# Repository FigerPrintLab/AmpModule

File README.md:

# AmpModule (Stakx)

Hardware implementation for the Stakx amplifier's front panel PCB.

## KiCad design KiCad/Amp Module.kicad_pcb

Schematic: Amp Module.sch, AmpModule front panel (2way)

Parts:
C1, C2: 22p; C_0805_2012Metric
C3, C4, C5, C6, C11, C12, C13, C14: 0.1uF; C_0805_2012Metric
C7: 10uF; CP_Elec_4x5.3
C8: 22uF; CP_Elec_4x5.3
C9, C10: 1u; C_0805_2012Metric
D1, D2: D_Small; D_MiniMELF
D3: READY1; LED_Rectangular_W5.0mm_H5.0mm
D4: READY2; LED_Rectangular_W5.0mm_H5.0mm
D5: ON; LED_Rectangular_W5.0mm_H5.0mm
J1: DSP; IDC-Header_2x17_P2.54mm_Vertical
J2: LITEMOD; IDC-Header_2x17_P2.54mm_Vertical
R1, R2: 8.2k; R_0805_2012Metric
R3, R4, R11, R17: 2.7k; R_0805_2012Metric
R5, R6, R13, R19: 1k; R_0805_2012Metric
R7, R8, R12, R18: 1.8k; R_0805_2012Metric
R9, R15: 5.6k; R_0805_2012Metric
R10, R16: 3.9k; R_0805_2012Metric
R14, R20: 470; R_0805_2012Metric
R21, R22, R27, R28, R29: 180; R_0805_2012Metric
R23, R24: 51k; R_0805_2012Metric
R25, R26: 22k; R_0805_2012Metric
SW1, SW2: Alps_SRBV170701
SW3: MUTE1; TL2-NNS7
SW4: MUTE2; TL2-NNS7
U1, U2: NE5532; SOIC-8_3.9x4.9mm_P1.27mm
U3: AMS1117-5.0; SOT-223-3_TabPin2
U4: TL072; SOIC-8_3.9x4.9mm_P1.27mm
U5: 74LVC2G14; SOT-23-6
U6: 74VHC74; TSSOP-14_4.4x5mm_P0.65mm
U7: 74HC08; SOIC-14_3.9x8.7mm_P1.27mm

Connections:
+5VDC: J1.4, J1.31, J2.4, J2.31
+5V_REG: C8.1, C11.2, C12.2, C13.2, C14.2, D5.2 (A), R21.1, R22.1, R23.1, R24.1, U3.2 (VO), U4.8 (V+), U5.5 (VCC), U6.1 (~R), U6.4 (~S), U6.10 (~S), U6.13 (~R), U6.14 (VCC), U7.14 (VCC); also elsewhere on the board
+12VDC: C5.1, C6.1, C7.1, J1.13, J1.22, J2.13, J2.22, U1.8 (V+), U2.8 (V+), U3.3 (VI)
+VCCMON: J1.16, J1.19, J2.16, J2.19
-12VDC: C3.1, C4.1, J1.14, J1.21, J2.14, J2.21, U1.4 (V-), U2.4 (V-)
-VCCMON: J1.17, J1.18, J2.17, J2.18
DSP_MUTE1: J1.15, U7.2
DSP_MUTE2: J1.20, U7.4
DSP_OUT1+: J1.6, R1.1
DSP_OUT1-: J1.7
DSP_OUT2+: J1.29, R2.1
DSP_OUT2-: J1.28
GND: C3.2, C4.2, C5.2, C6.2, C7.2, C8.2, C9.2, C10.2, C11.1, C12.1, C13.1, C14.1, J1.5, J1.8, J1.27, J1.30, J2.5, J2.8, J2.27, J2.30, R3.2, R4.2, R7.1, R8.1, R27.2, R28.2, R29.2, SW3.1, SW4.1, U3.1 (GND), U4.4 (V-), U5.2 (GND), U6.7 (GND), U7.7 (GND); also elsewhere on the board
IOUT1MON: J1.11, J2.11
IOUT2MON: J1.24, J2.24
LM_IN1+: J2.6, U1.6 (-), U1.7
LM_IN1-: J2.7
LM_IN2+: J2.29, U2.6 (-), U2.7
LM_IN2-: J2.28
LM_MUTE1: J2.15, SW3.3 (K), U7.3
LM_MUTE2: J2.20, SW4.3 (K), U7.6
unnamed: C1.1, SW1.1, SW1.10, U1.1, U1.5 (+)
unnamed: C1.2, R7.2, R9.1, R10.1, R11.1, R12.1, R13.1, R14.1, SW1.8, U1.2 (-)
unnamed: C2.1, SW2.1, SW2.10, U2.1, U2.5 (+)
unnamed: C2.2, R8.2, R15.1, R16.1, R17.1, R18.1, R19.1, R20.1, SW2.8, U2.2 (-)
unnamed: C9.1, D1.1 (K), R25.1, U5.1
unnamed: C10.1, D2.1 (K), R26.1, U5.3
unnamed: D1.2 (A), R23.2, R25.2, SW3.2
unnamed: D2.2 (A), R24.2, R26.2, SW4.2
unnamed 29: D3.1 (K), R27.1; also elsewhere on the board
unnamed: D4.1 (K), R28.1
unnamed: D5.1 (K), R29.1
unnamed: R1.2, R3.1, R5.2
unnamed: R2.2, R4.1, R6.2
unnamed: R5.1, U1.3 (+)
unnamed: R6.1, U2.3 (+)
unnamed: R9.2, SW1.2
unnamed: R10.2, SW1.3
unnamed: R11.2, SW1.4
unnamed: R12.2, SW1.5
unnamed: R13.2, SW1.6
unnamed: R14.2, SW1.7
unnamed: R15.2, SW2.2
unnamed: R16.2, SW2.3
unnamed: R17.2, SW2.4
unnamed: R18.2, SW2.5
unnamed: R19.2, SW2.6
unnamed: R20.2, SW2.7
unnamed: R21.2, SW3.4 (A)
unnamed: R22.2, SW4.4 (A)
unnamed: U5.4, U6.11 (C)
unnamed: U5.6, U6.3 (C)
unnamed: U6.2 (D), U6.6 (~Q)
unnamed: U6.5 (Q), U7.1
unnamed: U6.9 (Q), U7.5
unnamed: U6.8 (~Q), U6.12 (D)
PROTECT1: J1.10, J2.10; also elsewhere on the board
PROTECT2: J1.25, J2.25; also elsewhere on the board
READY1: J2.2, U4.3 (+)
READY2: J2.33, U4.5 (+)
READY_DSP1: D3.2 (A), J1.2, U4.1, U4.2 (-); also elsewhere on the board
READY_DSP2: D4.2 (A), J1.33, U4.6 (-), U4.7
RESERVED_A: J1.3, J2.3
RESERVED_B: J1.32, J2.32
SDPWS: J1.1, J1.34, J2.1, J2.34
TEMPMON12: J1.12, J1.23, J2.12, J2.23; also elsewhere on the board
VOUT1MON: J1.9, J2.9; also elsewhere on the board
VOUT2MON: J1.26, J2.26; also elsewhere on the board

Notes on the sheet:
IDC
MUTE
AUDIO
STATUS LEDs
REGULATOR
check cap

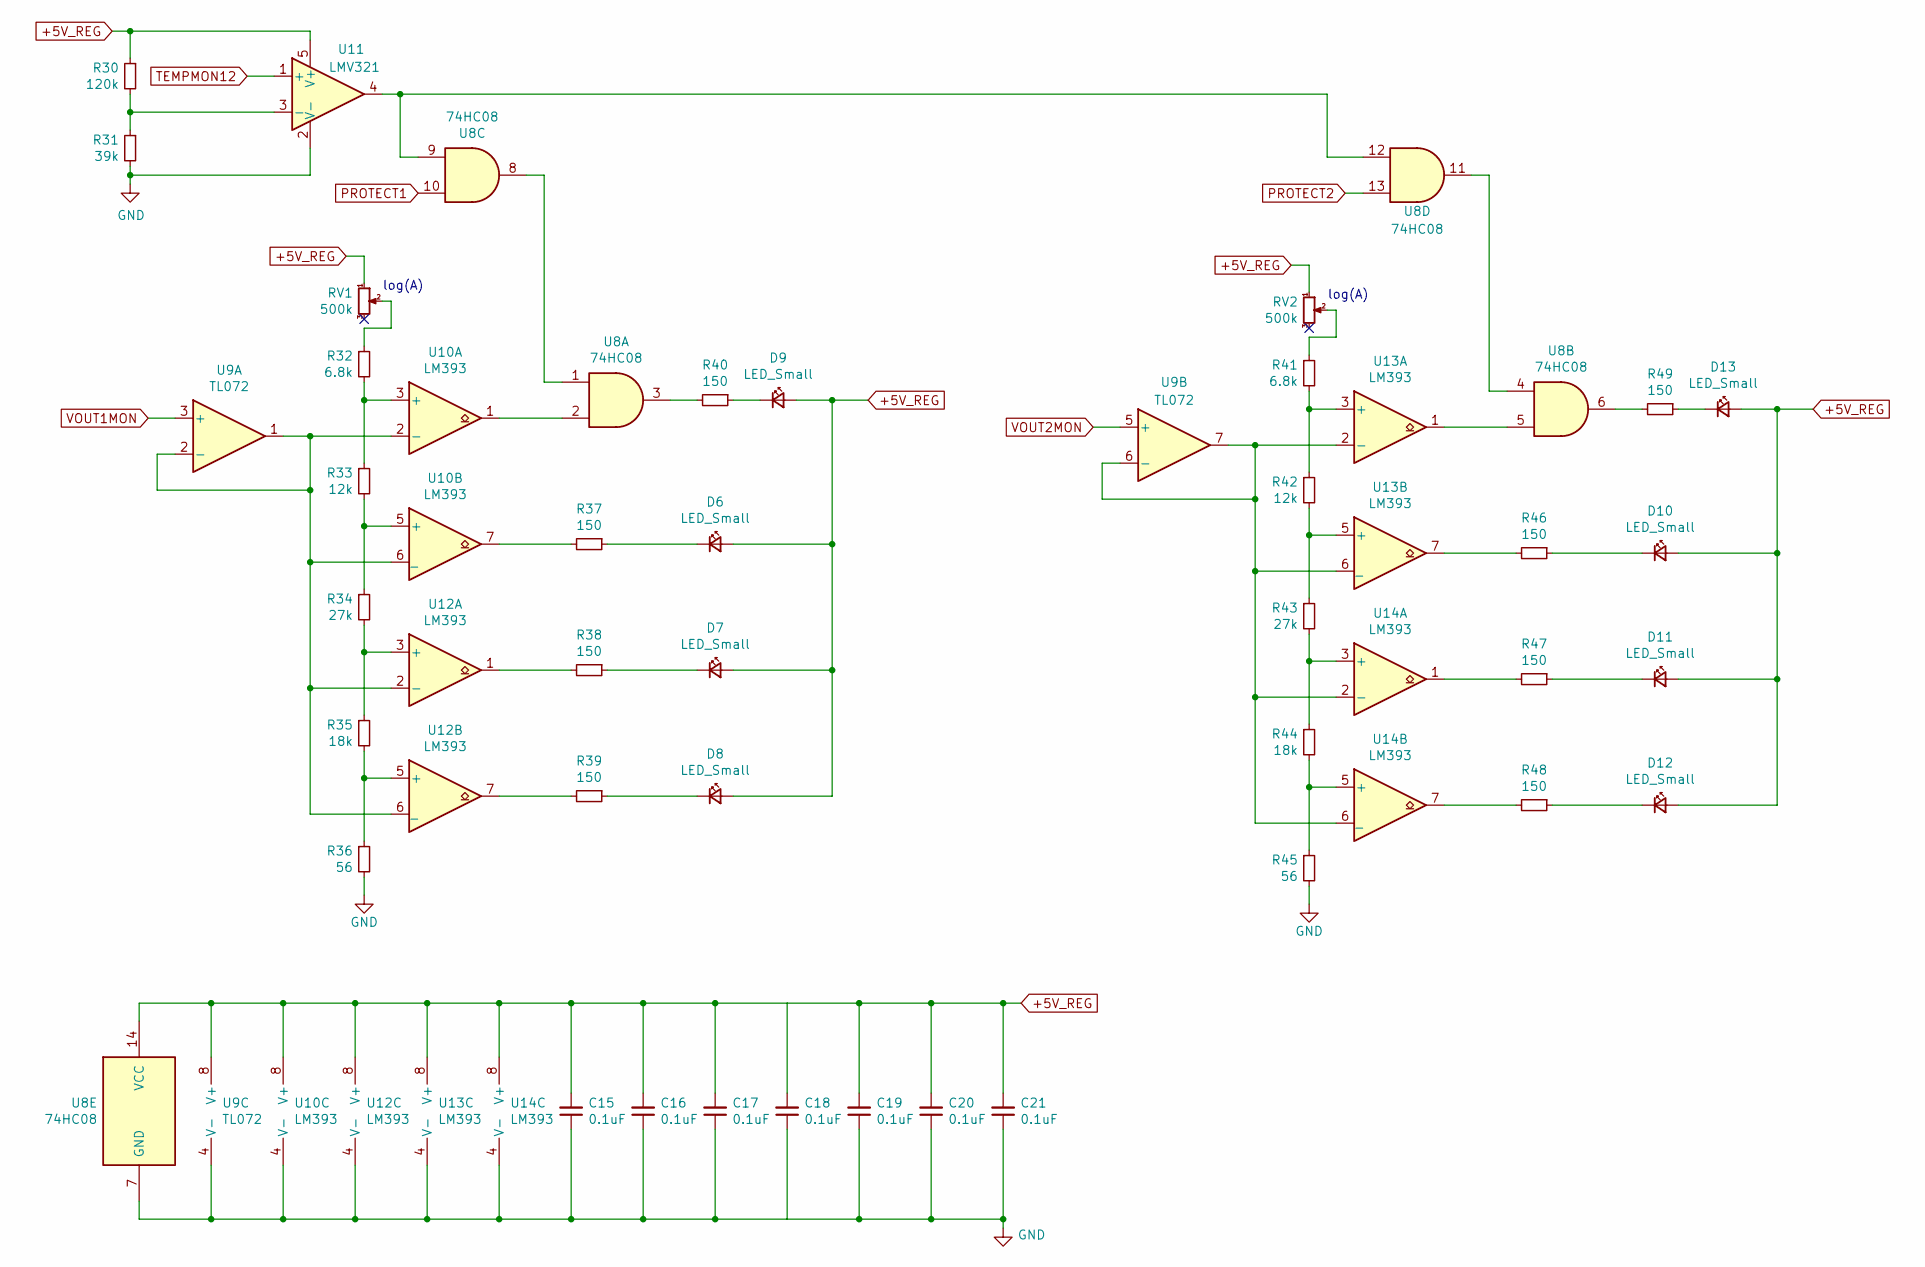
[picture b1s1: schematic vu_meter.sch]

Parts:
C15, C16, C17, C18, C19, C20, C21: 0.1uF; C_0805_2012Metric
D6, D7, D8, D9, D10, D11, D12, D13: LED_Small; LED_Rectangular_W5.0mm_H5.0mm
R30: 120k; R_0805_2012Metric
R31: 39k; R_0805_2012Metric
R32, R41: 6.8k; R_0805_2012Metric
R33, R42: 12k; R_0805_2012Metric
R34, R43: 27k; R_0805_2012Metric
R35, R44: 18k; R_0805_2012Metric
R36, R45: 56; R_0805_2012Metric
R37, R38, R39, R40, R46, R47, R48, R49: 150; R_0805_2012Metric
RV1, RV2: 500k; Trim_audio
U8: 74HC08; SOIC-14_3.9x8.7mm_P1.27mm
U9: TL072; SOIC-8_3.9x4.9mm_P1.27mm
U10, U12, U13, U14: LM393; SOIC-8_3.9x4.9mm_P1.27mm
U11: LMV321; SOT-23-5

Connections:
+5V_REG: C15.2, C16.2, C17.2, C18.2, C19.2, C20.2, C21.2, D6.2 (A), D7.2 (A), D8.2 (A), D9.2 (A), D10.2 (A), D11.2 (A), D12.2 (A), D13.2 (A), R30.1, RV1.1, RV2.1, U8.14 (VCC), U9.8 (V+), U10.8 (V+), U11.5 (V+), U12.8 (V+), U13.8 (V+), U14.8 (V+); also elsewhere on the board
GND: C15.1, C16.1, C17.1, C18.1, C19.1, C20.1, C21.1, R31.2, R36.2, R45.2, U8.7 (GND), U9.4 (V-), U10.4 (V-), U11.2 (V-), U12.4 (V-), U13.4 (V-), U14.4 (V-); also elsewhere on the board
unnamed: D6.1 (K), R37.1
unnamed: D7.1 (K), R38.1
unnamed: D8.1 (K), R39.1
unnamed: D9.1 (K), R40.1
unnamed: D10.1 (K), R46.1
unnamed: D11.1 (K), R47.1
unnamed: D12.1 (K), R48.1
unnamed: D13.1 (K), R49.1
unnamed: R30.2, R31.1, U11.3 (-)
unnamed: R32.1, RV1.2
unnamed: R32.2, R33.1, U10.3 (+)
unnamed: R33.2, R34.1, U10.5 (+)
unnamed: R34.2, R35.1, U12.3 (+)
unnamed: R35.2, R36.1, U12.5 (+)
unnamed: R37.2, U10.7
unnamed: R38.2, U12.1
unnamed: R39.2, U12.7
unnamed: R40.2, U8.3
unnamed: R41.1, RV2.2
unnamed: R41.2, R42.1, U13.3 (+)
unnamed: R42.2, R43.1, U13.5 (+)
unnamed: R43.2, R44.1, U14.3 (+)
unnamed: R44.2, R45.1, U14.5 (+)
unnamed: R46.2, U13.7
unnamed: R47.2, U14.1
unnamed: R48.2, U14.7
unnamed: R49.2, U8.6
unnamed: U8.1, U8.8
unnamed: U8.4, U8.11
unnamed: U8.2, U10.1
unnamed: U9.1, U9.2 (-), U10.2 (-), U10.6 (_), U12.2 (-), U12.6 (_)
unnamed: U8.9, U8.12, U11.4
unnamed: U8.5, U13.1
unnamed: U9.6 (-), U9.7, U13.2 (-), U13.6 (_), U14.2 (-), U14.6 (_)
PROTECT1: U8.10; also elsewhere on the board
PROTECT2: U8.13; also elsewhere on the board
TEMPMON12: U11.1 (+); also elsewhere on the board
VOUT1MON: U9.3 (+); also elsewhere on the board
VOUT2MON: U9.5 (+); also elsewhere on the board

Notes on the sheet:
log(A)

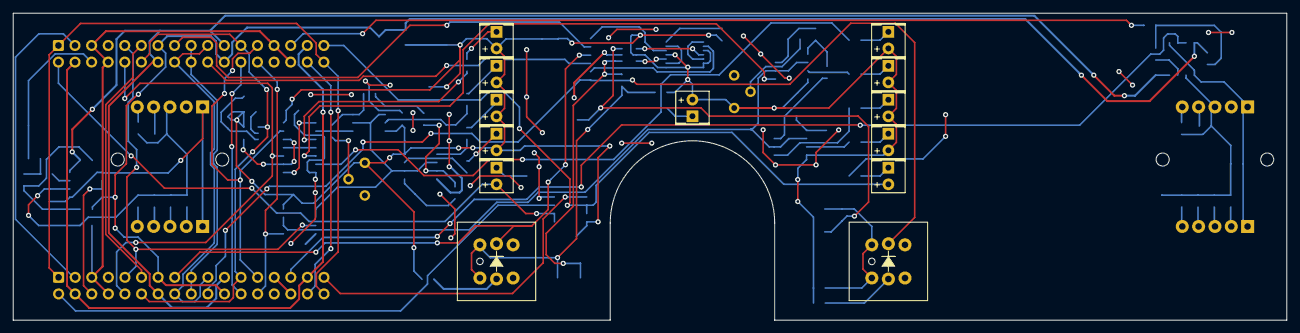
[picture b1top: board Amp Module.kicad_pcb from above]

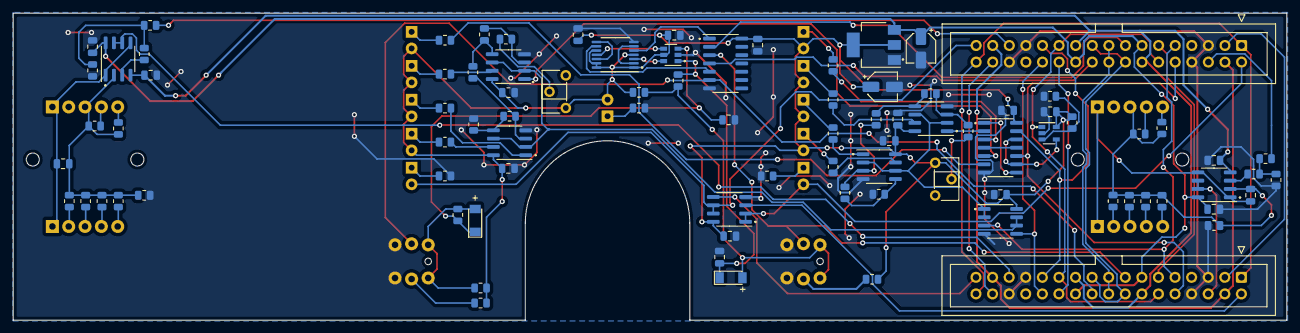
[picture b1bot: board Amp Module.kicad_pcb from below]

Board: 2 copper layers, 195.0 x 47.0 mm, 105 parts (90 on the bottom side), 98 nets.

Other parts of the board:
Deee: READY1; LED_Rectangular_W5.0mm_H5.0mm

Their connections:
unnamed 29: Deee.1; also elsewhere on the board
READY_DSP1: Deee.2; also elsewhere on the board

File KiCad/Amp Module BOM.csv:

Comment,Designator,Footprint,LCSC part number
22pF,"C1,C2",Capacitor_SMD:C_0805_2012Metric,C1804
0.1uF,"C3,C4,C5,C6,C11,C12,C13,C14,C15,C16,C17,C18,C19,C20,C21",Capacitor_SMD:C_0805_2012Metric,C28233
10uF,C7,Capacitor_SMD:CP_Elec_4x5.3,C72487
22uF,C8,Capacitor_SMD:CP_Elec_4x5.3,C72505
1uF,"C9,C10",Capacitor_SMD:C_0805_2012Metric,C28323
Diode,"D1,D2",Diode_SMD:D_MiniMELF,C9808
8.2k,"R1,R2",Resistor_SMD:R_0805_2012Metric,C17828
3.9k,"R10,R16",Resistor_SMD:R_0805_2012Metric,C17614
470,"R14,R20",Resistor_SMD:R_0805_2012Metric,C17710
51k,"R23,R24",Resistor_SMD:R_0805_2012Metric,C17737
22k,"R25,R26",Resistor_SMD:R_0805_2012Metric,C17560
180,"R21,R22,R27,R28,R29",Resistor_SMD:R_0805_2012Metric,C25270
2.7k,"R3,R4,R11,R17",Resistor_SMD:R_0805_2012Metric,C17530
120k,R30,Resistor_SMD:R_0805_2012Metric,C17436
39k,R31,Resistor_SMD:R_0805_2012Metric,C25826
6.8k,"R32,R41",Resistor_SMD:R_0805_2012Metric,C17772
12k,"R33,R42",Resistor_SMD:R_0805_2012Metric,C17444
27k,"R34,R43",Resistor_SMD:R_0805_2012Metric,C17593
18k,"R35,R44",Resistor_SMD:R_0805_2012Metric,C17506
56,"R36,R45",Resistor_SMD:R_0805_2012Metric,C17757
150,"R37,R38,R39,R40,R46,R47,R48,R49",Resistor_SMD:R_0805_2012Metric,C17471
1k,"R5,R6,R13,R19",Resistor_SMD:R_0805_2012Metric,C17513
1.8k,"R7,R8,R12,R18",Resistor_SMD:R_0805_2012Metric,C17398
5.6k,"R9,R15",Resistor_SMD:R_0805_2012Metric,C4382
NE5532DR,"U1,U2",Package_SO:SOIC-8_3.9x4.9mm_P1.27mm,C7426
LMV321IDBVR,U11,Package_TO_SOT_SMD:SOT-23-5,C7972
LM393DR2G,"U10,U12,U13,U14",Package_SO:SOIC-8_3.9x4.9mm_P1.27mm,C7955
AMS1117-5.0,U3,Package_TO_SOT_SMD:SOT-223-3_TabPin2,C6187
TL072CDT,"U4,U9",Package_SO:SOIC-8_3.9x4.9mm_P1.27mm,C6961
74LVC2G14W6-7,U5,Package_TO_SOT_SMD:SOT-23-6,C384558
74VHC74MTCX,U6,Package_SO:TSSOP-14_4.4x5mm_P0.65mm,C6153
"74HC08D,653","U7,U8",Package_SO:SOIC-14_3.9x8.7mm_P1.27mm,C5593

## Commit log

2020-12-03 update KiCad folder
2020-12-03 update 'Logic scheme.png'
2020-12-05 Update schematics
2020-12-06 Update schematic
2020-12-18 schematic updated
2020-12-19 updated schematic
2021-01-06 figerprint icon
2021-02-28 added flow chart
2021-02-28 first 2way commit
2021-02-28 added basic filter and trim
2021-03-01 added questions file
2021-03-01 restored filter and added initial attenuation in trim
2021-03-01 added new question
2021-03-01 added answers
2021-03-02 MiniAMP_POC_Render
    Proof Of Concept of the MiniAMP Mechanical design
2021-03-02 changed Q to a fixed value
2021-03-03 moved initial attenuation to filter input
2021-03-06 saved from laptop and added new questions
2021-03-16 updated schematic to latest KiCad version
2021-03-18 removed VU Meter sheet
2021-03-20 changed 4053 to DG419 & added negative latch
2021-04-30 added custom VU meter
2021-04-30 first single IDC commit
2021-08-11 linux friendly filenames
2021-09-16 freeze at 3 leds
2021-09-25 schematic completed
2021-09-25 exported pdf
2021-09-28 edited chez Gabri's
2021-09-28 added bom
2021-10-20 finished PCB with TL12
2021-10-20 changed to TL2
2021-10-23 corrected rotary switch footprint
2021-10-23 started BOM export
2021-10-24 exported BOM and pos
2021-10-24 preparing merge from 2ohms
2021-10-24 exported gerbers and all JLC files
2021-10-24 moved some traces
2021-10-25 rotated LEDs and cutted PCB
2021-10-25 exported JLC files
2021-10-25 added mark on pin #1 on silkscreen
